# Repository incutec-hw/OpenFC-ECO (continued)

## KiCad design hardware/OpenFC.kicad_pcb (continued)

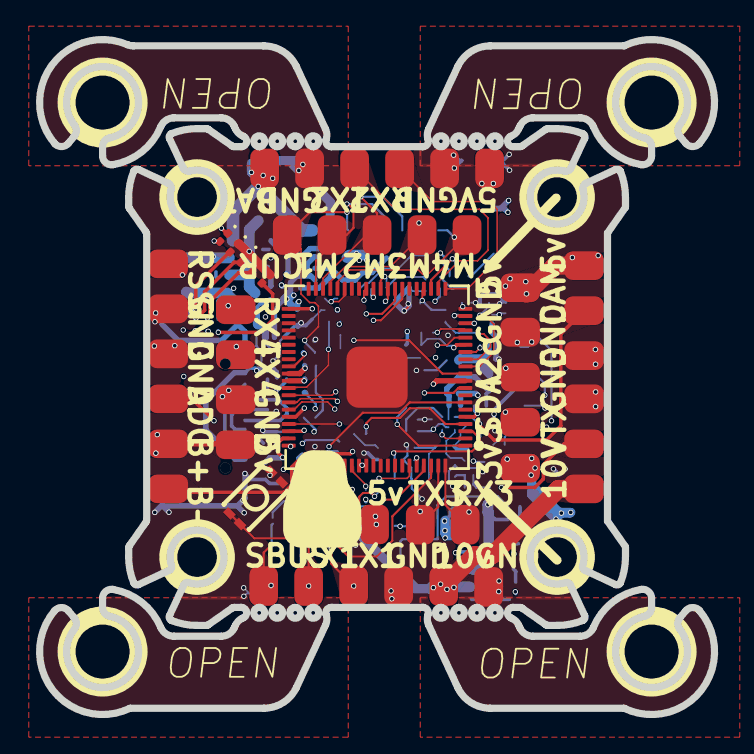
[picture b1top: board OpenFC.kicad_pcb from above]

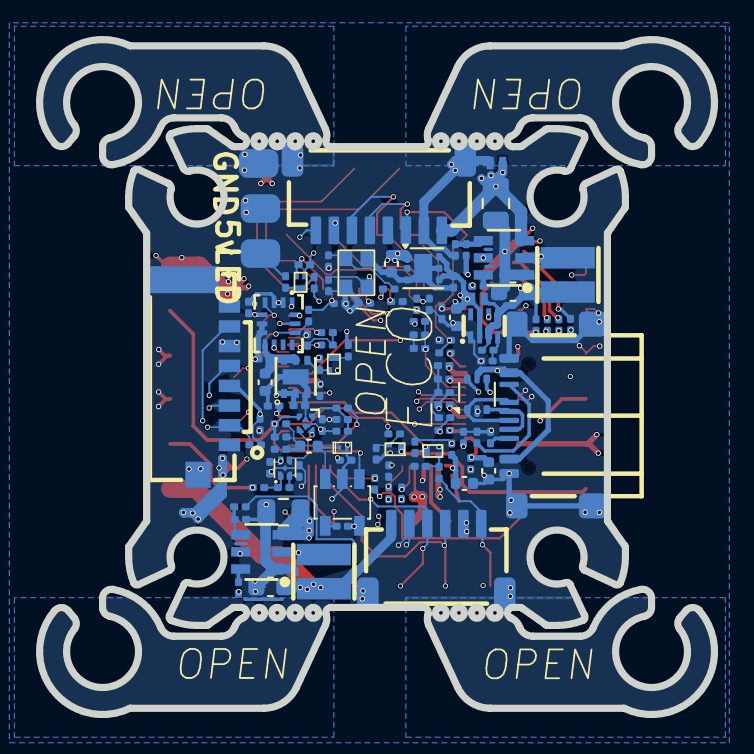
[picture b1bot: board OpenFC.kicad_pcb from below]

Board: 6 copper layers, 37.5 x 37.5 mm, 164 parts (113 on the bottom side), 93 nets.

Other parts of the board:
C35, C36: 100n; C_0201_0603Metric
U9: LSM6DSV16XTR; LGA-14_L3.0-W2.5-P0.50-BR

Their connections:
+1.8V_GYRO: C35.1, U9.8 (Vdd); also elsewhere on the board
/IMU/GYRO_CS: U9.12 (CS); also elsewhere on the board
/IMU/GYRO_INT: U9.4 (INT1); also elsewhere on the board
/IMU/SPI0.CLKIN: U9.9 (INT2); also elsewhere on the board
/IMU/SPI0.MISO: U9.1 (SDO/SA0); also elsewhere on the board
/IMU/SPI0.MOSI: U9.14 (SDA); also elsewhere on the board
/IMU/SPI0.SCK: U9.13 (SCL); also elsewhere on the board
GND: C35.2, C36.2, U9.2 (SDx/AH1/Qvar1), U9.3 (SCx/AH2/Qvar2), U9.6 (GND), U9.7 (GND); also elsewhere on the board

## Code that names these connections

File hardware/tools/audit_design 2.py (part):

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    # ---- 3. Power tree ----
    W("## 3. Power Tree\n")
    W("```")
    W("+BATT -> U6 (LMR51420YFDDCR buck) -> +12V   [switchable via GPIO11 via Q?]")
    W("+BATT -> U7 (LMR51420YFDDCR buck) -> +5V_BUCK")
    W("+5V_BUCK -+")
    W("          +- U33 (TPS2116 mux) -> +5V")
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                     ", ".join(caps) or "**NONE**"])
    W(md_table(["Role", "Net", "MCU pad", "Resistors on net", "Bypass caps to GND"], rows))
    W("")
    W("**Check**: A CURRENT-sense ADC input WITHOUT a bypass cap at the MCU pin is a "
      "Betaflight MFG-guideline violation (noise couples straight into ADC).\n")

    # ---- 6. SPI buses & CS pull-ups ----
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    W("## 15. CLAUDE.md GPIO map cross-check\n")
    # From CLAUDE.md
    claude_gpio = {
        "GPIO0":  "UART0 TX",
        "GPIO1":  "UART0 RX",
        "GPIO2":  "PIO UART0 TX",
        "GPIO3":  "PIO UART0 RX",
        "GPIO6":  "Beeper",
        "GPIO11": "10V enable",
        "GPIO12": "Status LED",
        "GPIO13": "IMU INT",
        "GPIO14": "IMU CS",
        "GPIO18": "IMU SCK",
        "GPIO19": "IMU MISO",
        "GPIO20": "IMU MOSI",
        "GPIO21": "UART1 RX",
        "GPIO22": "UART1 TX",
        "GPIO23": "LED strip",
        "GPIO26": "PIO UART1 TX",
        "GPIO27": "PIO UART1 RX",
        "GPIO28": "M4",
        "GPIO29": "M3",
        "GPIO30": "M2",
        "GPIO31": "M1",
        "GPIO32": "OSD VBLACK",
        "GPIO33": "OSD SYNC_IN",
        "GPIO34": "OSD PIXEL_SEL",
        "GPIO35": "OSD VWHITE",
        "GPIO36": "OSD COLOR_SEL",
        "GPIO37": "OSD SYNCLVL",
        "GPIO40": "CURRENT ADC",
        "GPIO41": "VBAT ADC",
        "GPIO45": "RSSI ADC",
        "GPIO47": "EXT ADC",
    }
    # Build GPIO# -> (pad, net) map from U36 pin functions
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        cn = curr_candidates[0]
        caps = find_caps_between({}, net2rp, cn, "GND")
        if not caps:
            findings.append(("HIGH", f"CURRENT-sense net `{cn}` has NO bypass cap to GND — add ~100nF near MCU ADC pin."))
    # VBAT bypass
    vb_candidates = [n for n in net2rp if re.search(r"VBAT.*SENSE|VBAT_?ADC", n, re.I)]
    if vb_candidates:
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
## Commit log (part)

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2026-04-06 Update power specifications in README
2026-05-07 alpha routing
